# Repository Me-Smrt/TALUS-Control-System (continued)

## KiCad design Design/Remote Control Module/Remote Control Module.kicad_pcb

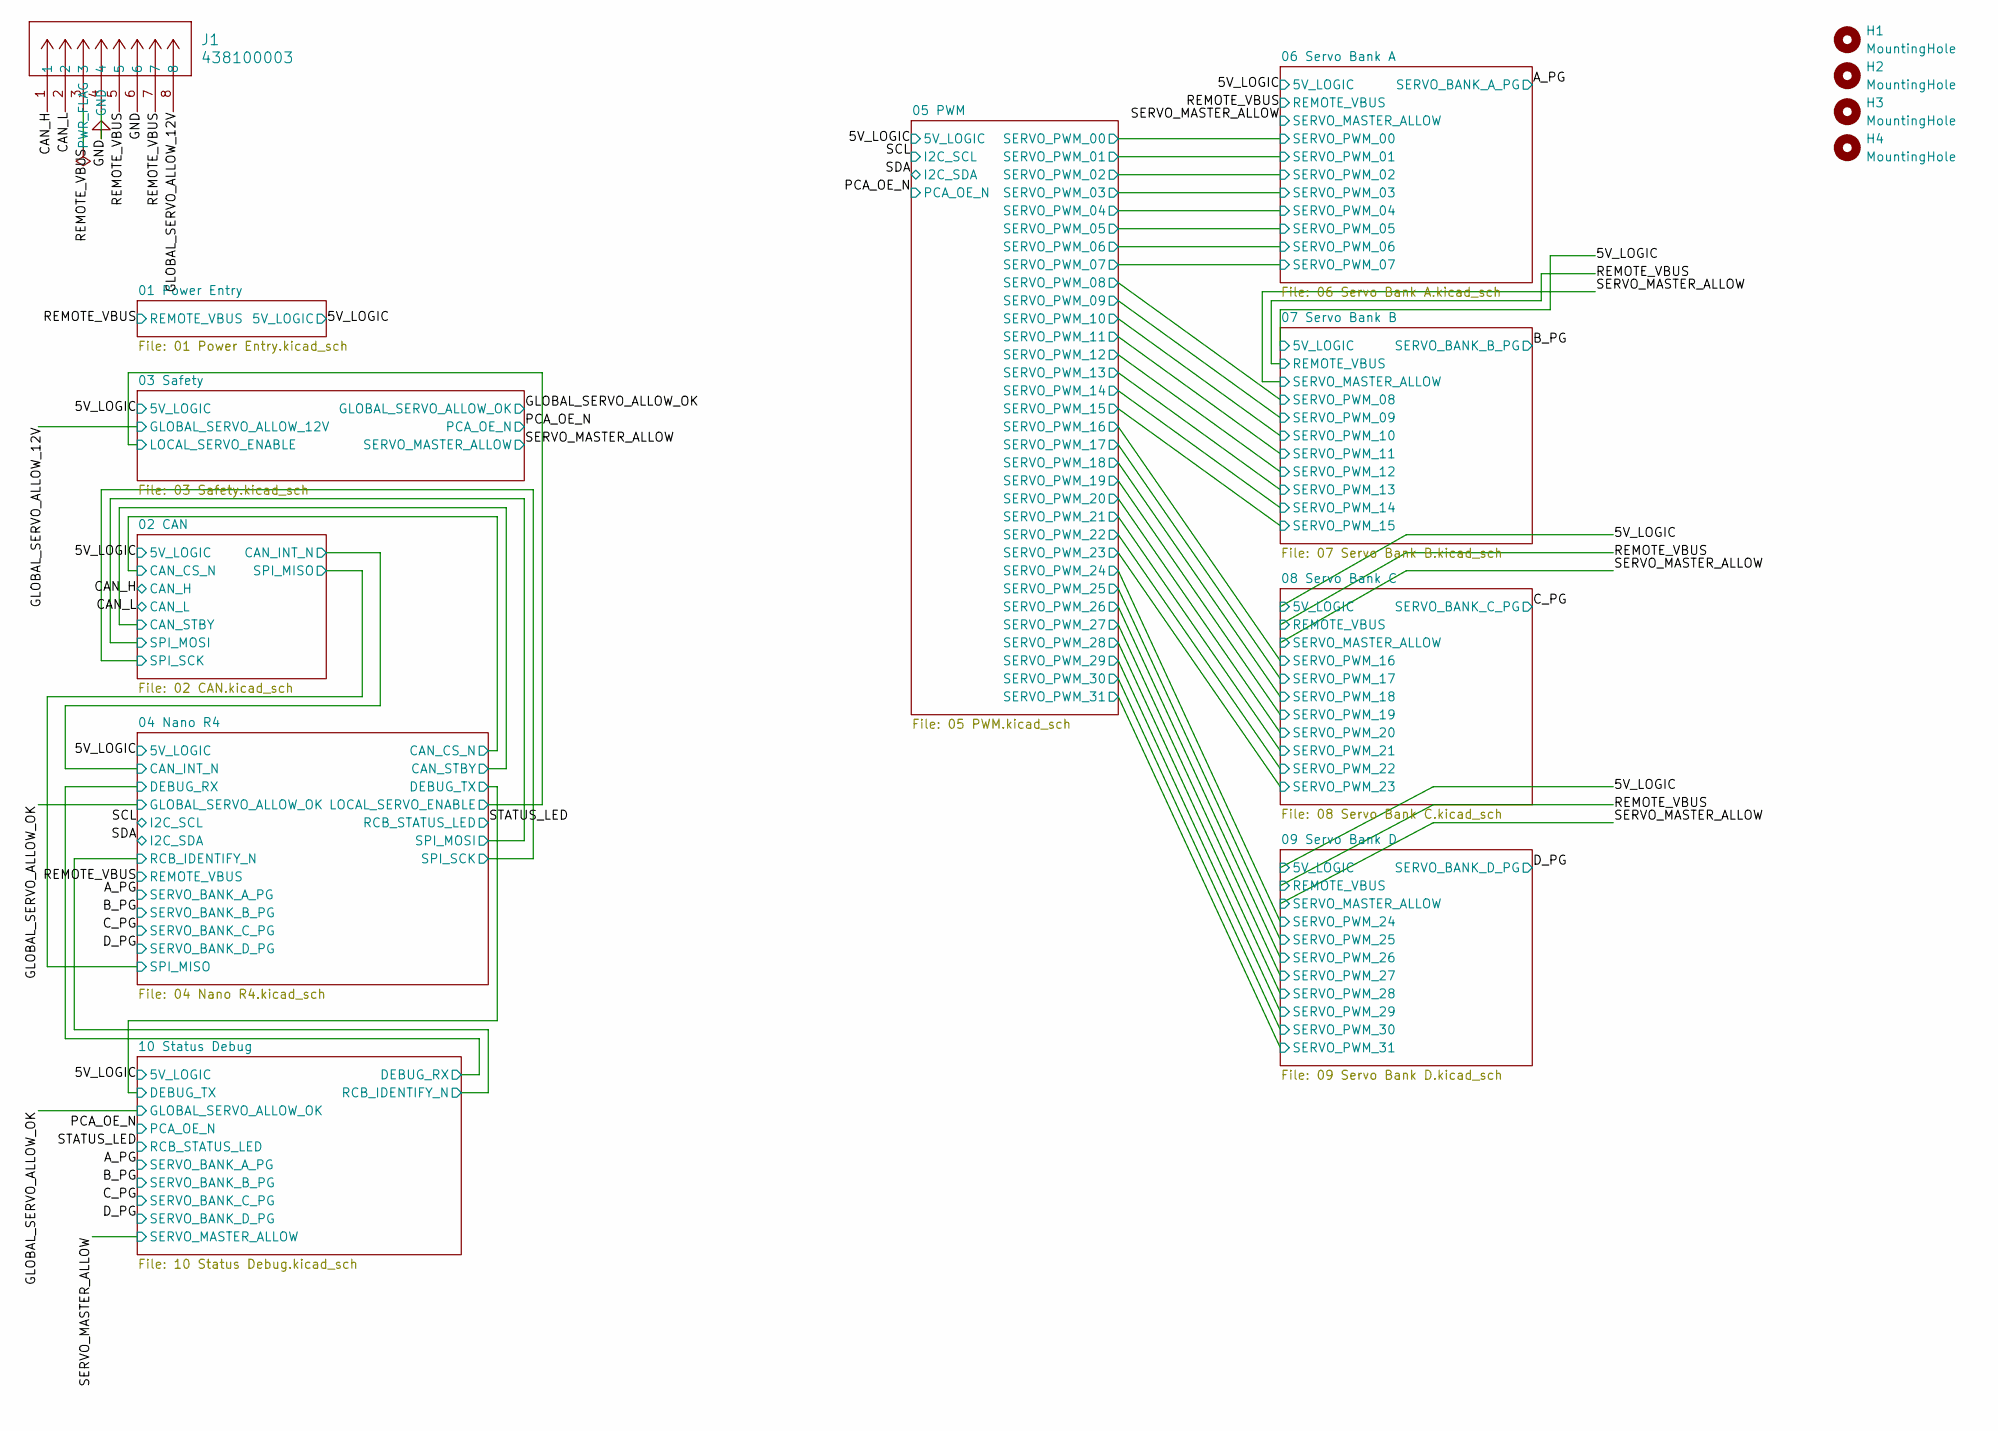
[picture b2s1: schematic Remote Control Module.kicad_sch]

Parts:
H1, H2, H3, H4: MountingHole; MountingHole_2.2mm_M2
J1: 438100003; CONN_SD-43810-011_08_CLIP_MOL; MPN 0438100003

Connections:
/CAN_H: J1.1; also elsewhere on the board
/CAN_L: J1.2; also elsewhere on the board
/GLOBAL_SERVO_ALLOW_12V: J1.8; also elsewhere on the board
/REMOTE_VBUS: J1.3, J1.5, J1.7; also elsewhere on the board
GND: J1.4, J1.6; also elsewhere on the board

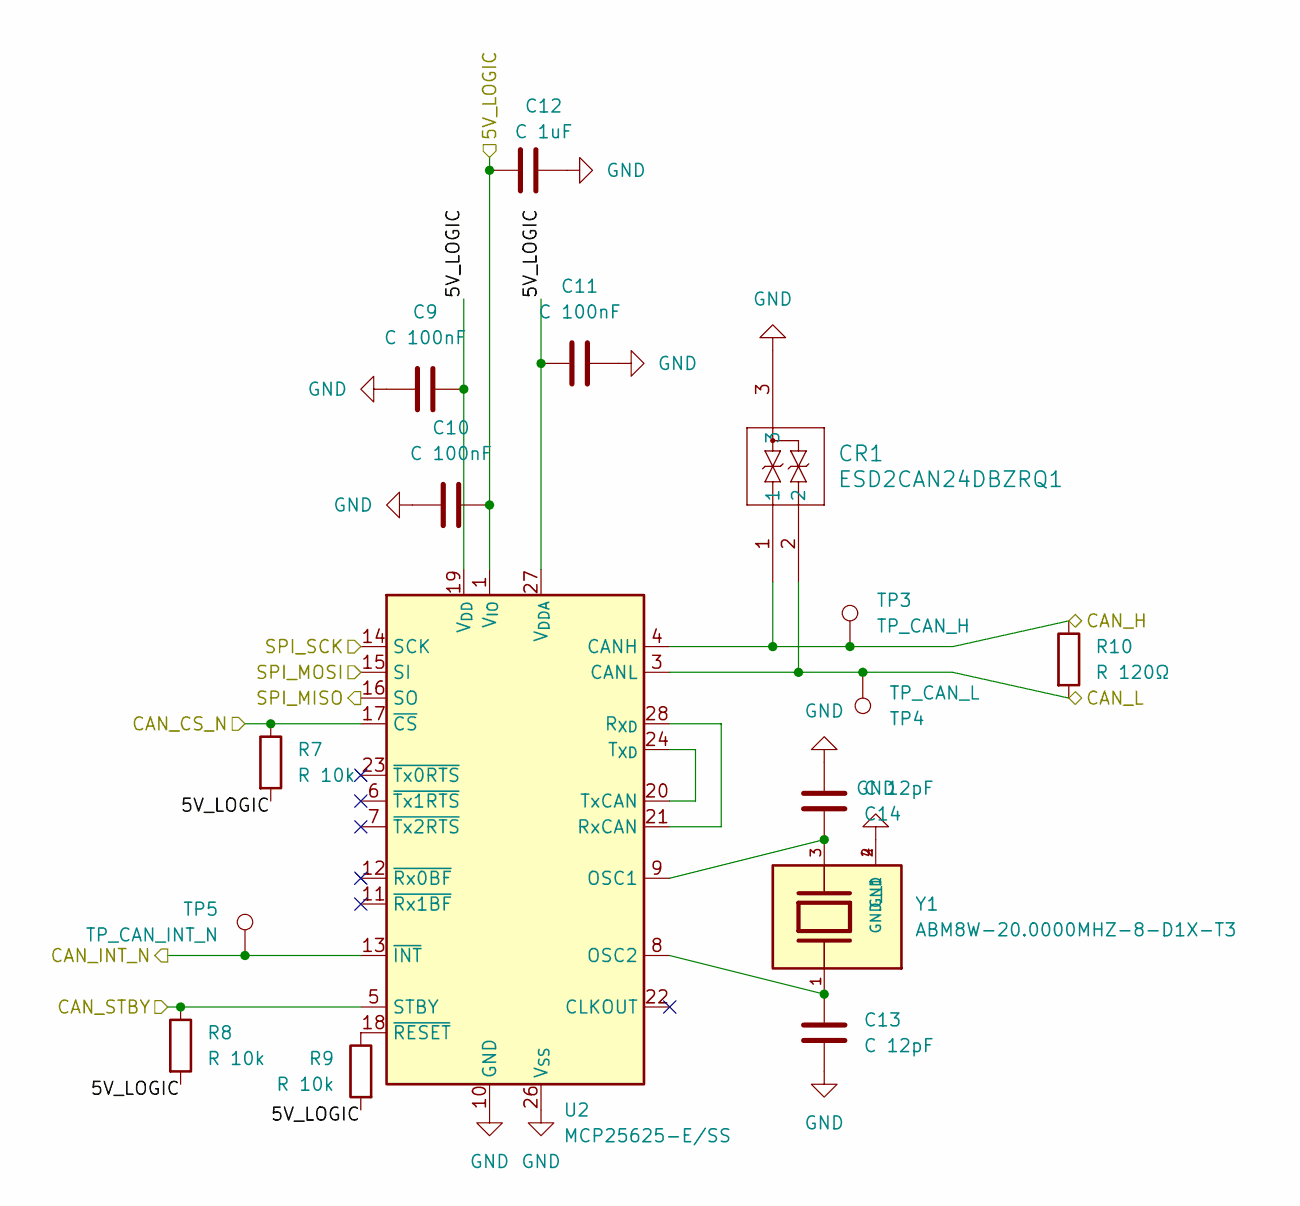
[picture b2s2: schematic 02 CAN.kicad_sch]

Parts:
C9, C10, C11: C 100nF; C_0603_1608Metric; MPN C0603C104K5RACAUTO
C12: C 1uF; C_0805_2012Metric; MPN CL21B105KBFNFNE
C13, C14: C 12pF; C_0603_1608Metric; MPN GRM1885C2A120JA01D
CR1: ESD2CAN24DBZRQ1; MPN ESD2CAN24DBZRQ1
R7, R8, R9: R 10k; R_0603_1608Metric; MPN RC0603FR-0710KL
R10: R 120Ω; R_0805_2012Metric; MPN RC0805FR-07120RL
TP3: TP_CAN_H; TestPoint_Pad_D1.5mm
TP4: TP_CAN_L; TestPoint_Pad_D1.5mm
TP5: TP_CAN_INT_N; TestPoint_Pad_D1.5mm
U2: MCP25625-E/SS; SSOP-28_5.3x10.2mm_P0.65mm; MPN MCP25625-E/SS
Y1: ABM8W-20.0000MHZ-8-D1X-T3; ABM8W 20 MHz; PARTREV 08.09.2018

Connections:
/02 CAN/CAN_CS_N: R7.1, U2.17 (~CS); also elsewhere on the board
/02 CAN/CAN_INT_N: TP5.1 (1_1), U2.13 (~INT); also elsewhere on the board
/02 CAN/CAN_STBY: R8.1, U2.5 (STBY); also elsewhere on the board
/02 CAN/SPI_MISO: U2.16 (SO); also elsewhere on the board
/02 CAN/SPI_MOSI: U2.15 (SI); also elsewhere on the board
/02 CAN/SPI_SCK: U2.14 (SCK); also elsewhere on the board
/5V_LOGIC: C9.2, C10.2, C11.2, C12.2, R7.2, R8.2, R9.2, U2.1 (V_{IO}), U2.19 (V_{DD}), U2.27 (V_{DDA}); also elsewhere on the board
/CAN_H: CR1.1, R10.1, TP3.1 (1_1), U2.4 (CANH); also elsewhere on the board
/CAN_L: CR1.2, R10.2, TP4.1 (1_1), U2.3 (CANL); also elsewhere on the board
GND: C9.1, C10.1, C11.1, C12.1, C13.2, C14.2, CR1.3, U2.10 (GND), U2.26 (V_{SS}), Y1.2 (GND), Y1.4 (GND__1); also elsewhere on the board
unnamed: C14.1, U2.9 (OSC1), Y1.3
unnamed: C13.1, U2.8 (OSC2), Y1.1
unnamed: U2.21 (RxCAN), U2.28 (R_{XD})
unnamed: U2.20 (TxCAN), U2.24 (T_{XD})
unnamed: R9.1, U2.18 (~RESET)

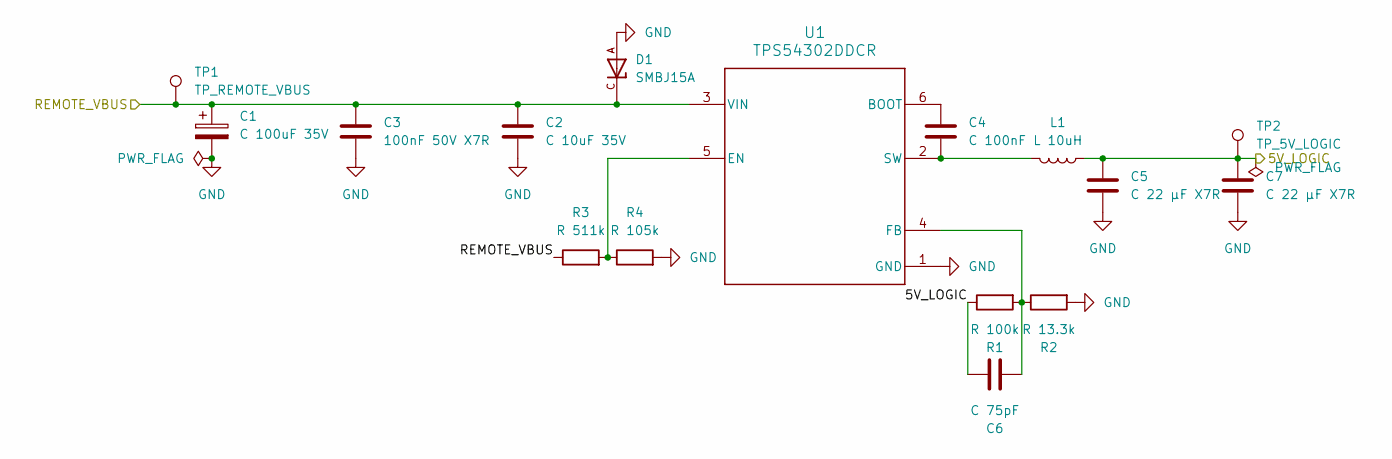
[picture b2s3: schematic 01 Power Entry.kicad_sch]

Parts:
C1: C 100uF 35V; EEEFK1V101P; MPN EEE-FK1V101P
C2: C 10uF 35V; C_1210_3225Metric; MPN CC1210KKX7RGBB106
C3: 100nF 50V X7R; C0603C104K5RACAUTO; MPN C0603C104K5RACAUTO
C4: C 100nF; C_0603_1608Metric; MPN C0603C104K5RACAUTO
C5, C7: C 22 µF X7R; C_1210_3225Metric; MPN GRM32ER71E226KE15L
C6: C 75pF; GRM1885C1H750JA01D; MPN GRM1885C2A750JA01D
D1: SMBJ15A; DIOM4336X265N; PARTREV F2102
L1: L 10uH; 7447714100; MPN 7447714100
R1: R 100k; R_0603_1608Metric; MPN RC0603FR-07100KL
R2: R 13.3k; R_0603_1608Metric; MPN RC0603FR-0713K3L
R3: R 511k; R_0603_1608Metric; MPN RC0603FR-07511KL
R4: R 105k; R_0603_1608Metric; MPN RC0603FR-07105KL
TP1: TP_REMOTE_VBUS; TestPoint_Pad_D1.5mm
TP2: TP_5V_LOGIC; TestPoint_Pad_D1.5mm
U1: TPS54302DDCR; MPN TPS54302DDCR

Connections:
/5V_LOGIC: C5.1, C6.1, C7.1, L1.1, R1.1, TP2.1 (1_1); also elsewhere on the board
/REMOTE_VBUS: C1.1, C2.1, C3.1, D1.C, R3.1, TP1.1 (1_1), U1.3 (VIN); also elsewhere on the board
GND: C1.2, C2.2, C3.2, C5.2, C7.2, D1.A, R2.2, R4.2, U1.1 (GND); also elsewhere on the board
unnamed: C4.1, U1.6 (BOOT)
unnamed: R3.2, R4.1, U1.5 (EN)
unnamed: C6.2, R1.2, R2.1, U1.4 (FB)
unnamed: C4.2, L1.2, U1.2 (SW)

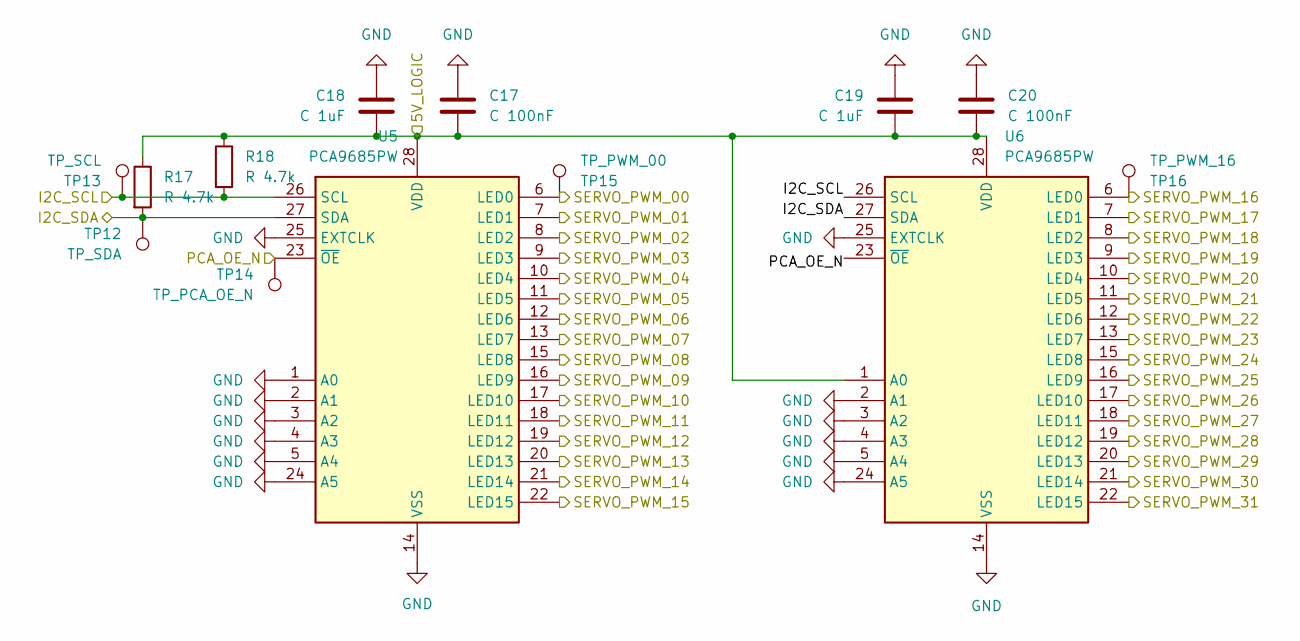
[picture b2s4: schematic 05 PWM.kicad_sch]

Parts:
C17, C20: C 100nF; C_0603_1608Metric; MPN C0603C104K5RACAUTO
C18, C19: C 1uF; C_0805_2012Metric; MPN CL21B105KBFNFNE
R17, R18: R 4.7k; R_0603_1608Metric; MPN RC0603FR-074K7L
TP12: TP_SDA; TestPoint_Pad_D1.5mm
TP13: TP_SCL; TestPoint_Pad_D1.5mm
TP14: TP_PCA_OE_N; TestPoint_Pad_D1.5mm
TP15: TP_PWM_00; TestPoint_Pad_D1.5mm
TP16: TP_PWM_16; TestPoint_Pad_D1.5mm
U5, U6: PCA9685PW; TSSOP-28_4.4x9.7mm_P0.65mm; MPN PCA9685PW,118

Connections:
/05 PWM/SERVO_PWM_00: TP15.1 (1_1), U5.6 (LED0); also elsewhere on the board
/05 PWM/SERVO_PWM_01: U5.7 (LED1); also elsewhere on the board
/05 PWM/SERVO_PWM_02: U5.8 (LED2); also elsewhere on the board
/05 PWM/SERVO_PWM_03: U5.9 (LED3); also elsewhere on the board
/05 PWM/SERVO_PWM_04: U5.10 (LED4); also elsewhere on the board
/05 PWM/SERVO_PWM_05: U5.11 (LED5); also elsewhere on the board
/05 PWM/SERVO_PWM_06: U5.12 (LED6); also elsewhere on the board
/05 PWM/SERVO_PWM_07: U5.13 (LED7); also elsewhere on the board
/05 PWM/SERVO_PWM_08: U5.15 (LED8); also elsewhere on the board
/05 PWM/SERVO_PWM_09: U5.16 (LED9); also elsewhere on the board
/05 PWM/SERVO_PWM_10: U5.17 (LED10); also elsewhere on the board
/05 PWM/SERVO_PWM_11: U5.18 (LED11); also elsewhere on the board
/05 PWM/SERVO_PWM_12: U5.19 (LED12); also elsewhere on the board
/05 PWM/SERVO_PWM_13: U5.20 (LED13); also elsewhere on the board
/05 PWM/SERVO_PWM_14: U5.21 (LED14); also elsewhere on the board
/05 PWM/SERVO_PWM_15: U5.22 (LED15); also elsewhere on the board
/05 PWM/SERVO_PWM_16: TP16.1 (1_1), U6.6 (LED0); also elsewhere on the board
/05 PWM/SERVO_PWM_17: U6.7 (LED1); also elsewhere on the board
/05 PWM/SERVO_PWM_18: U6.8 (LED2); also elsewhere on the board
/05 PWM/SERVO_PWM_19: U6.9 (LED3); also elsewhere on the board
/05 PWM/SERVO_PWM_20: U6.10 (LED4); also elsewhere on the board
/05 PWM/SERVO_PWM_21: U6.11 (LED5); also elsewhere on the board
/05 PWM/SERVO_PWM_22: U6.12 (LED6); also elsewhere on the board
/05 PWM/SERVO_PWM_23: U6.13 (LED7); also elsewhere on the board
/05 PWM/SERVO_PWM_24: U6.15 (LED8); also elsewhere on the board
/05 PWM/SERVO_PWM_25: U6.16 (LED9); also elsewhere on the board
/05 PWM/SERVO_PWM_26: U6.17 (LED10); also elsewhere on the board
/05 PWM/SERVO_PWM_27: U6.18 (LED11); also elsewhere on the board
/05 PWM/SERVO_PWM_28: U6.19 (LED12); also elsewhere on the board
/05 PWM/SERVO_PWM_29: U6.20 (LED13); also elsewhere on the board
/05 PWM/SERVO_PWM_30: U6.21 (LED14); also elsewhere on the board
/05 PWM/SERVO_PWM_31: U6.22 (LED15); also elsewhere on the board
/5V_LOGIC: C17.2, C18.2, C19.2, C20.2, R17.1, R18.1, U5.28 (VDD), U6.1 (A0), U6.28 (VDD); also elsewhere on the board
/PCA_OE_N: TP14.1 (1_1), U5.23 (~OE), U6.23 (~OE); also elsewhere on the board
/SCL: R18.2, TP13.1 (1_1), U5.26 (SCL), U6.26 (SCL); also elsewhere on the board
/SDA: R17.2, TP12.1 (1_1), U5.27 (SDA), U6.27 (SDA); also elsewhere on the board
GND: C17.1, C18.1, C19.1, C20.1, U5.1 (A0), U5.2 (A1), U5.3 (A2), U5.4 (A3), U5.5 (A4), U5.14 (VSS), U5.24 (A5), U5.25 (EXTCLK), U6.2 (A1), U6.3 (A2), U6.4 (A3), U6.5 (A4), U6.14 (VSS), U6.24 (A5), U6.25 (EXTCLK); also elsewhere on the board

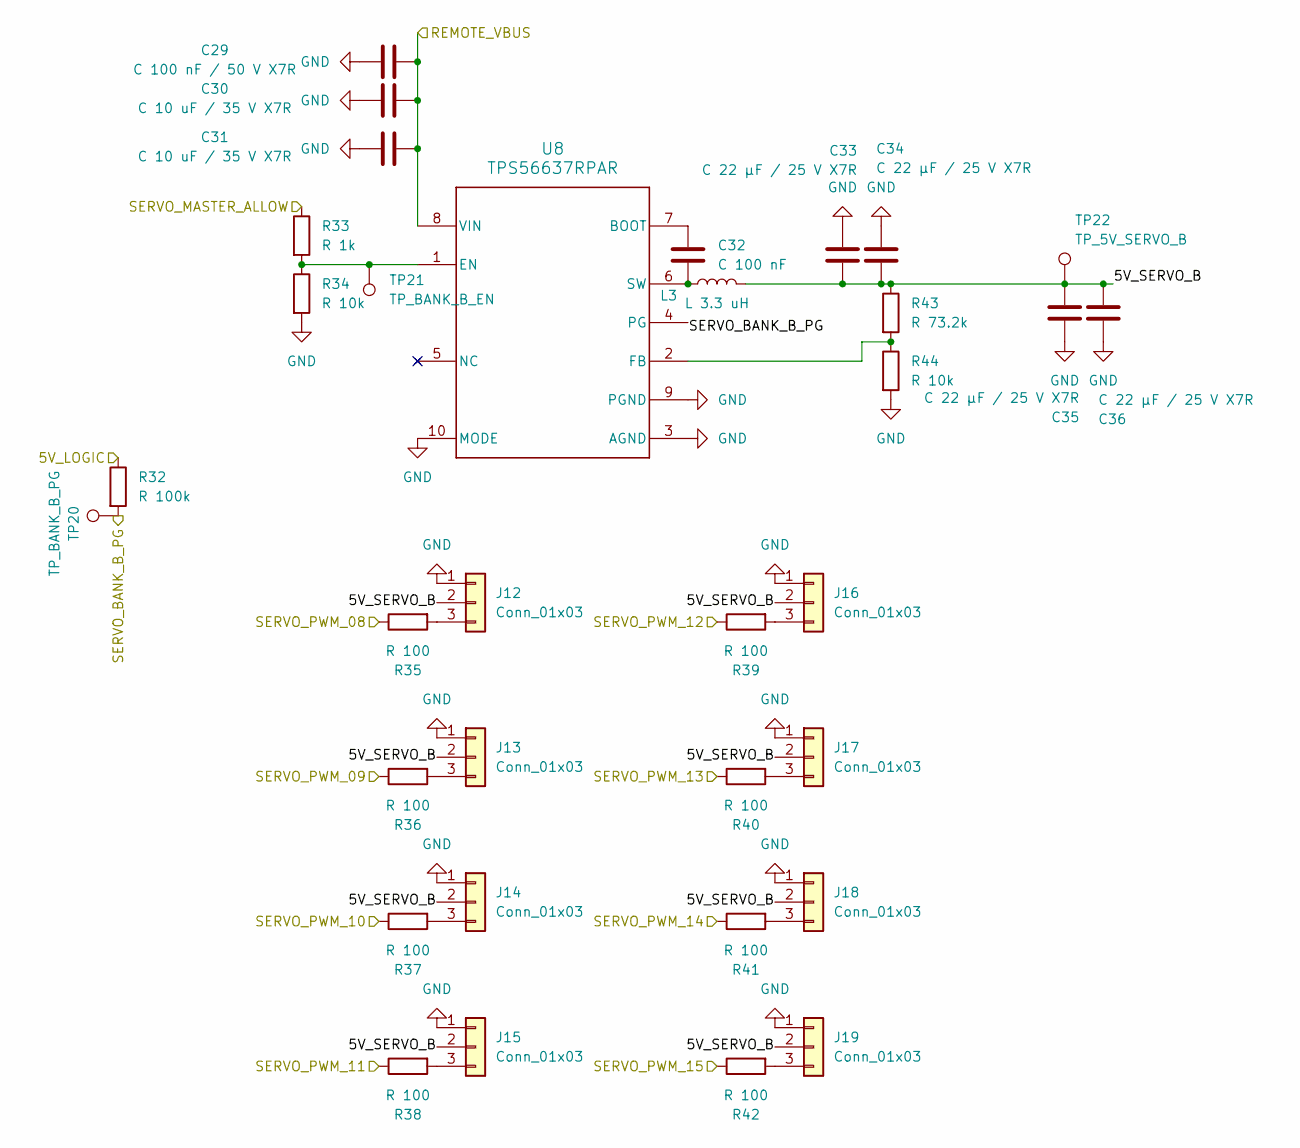
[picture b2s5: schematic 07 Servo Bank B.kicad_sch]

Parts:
C29: C 100 nF / 50 V X7R; C0603C104K5RACAUTO; MPN C0603C104K5RACAUTO
C30, C31: C 10 uF / 35 V X7R; C_1210_3225Metric; MPN CC1210KKX7RGBB106
C32: C 100 nF; C_0603_1608Metric; MPN C0603C104K5RACAUTO
C33, C34, C35, C36: C 22 µF / 25 V X7R; C_1210_3225Metric; MPN GRM32ER71E226KE15L
J12, J13, J14, J15, J16, J17, J18, J19: Conn_01x03; PinHeader_1x03_P2.54mm_Vertical_CompactSilk; MPN TSW-103-07-G-S
L3: L 3.3 uH; IND_IHLP-3232DZ_VIS; MPN IHLP3232DZER3R3M11
R32: R 100k; R_0603_1608Metric; MPN RC0603FR-07100KL
R33: R 1k; R_0603_1608Metric; MPN RC0603FR-071KL
R34, R44: R 10k; R_0603_1608Metric; MPN RC0603FR-0710KL
R35, R36, R37, R38, R39, R40, R41, R42: R 100; R_0603_1608Metric; MPN RC0603FR-07100RL
R43: R 73.2k; R_0603_1608Metric; MPN RC0603FR-0773K2L
TP20: TP_BANK_B_PG; TestPoint_Pad_D1.5mm
TP21: TP_BANK_B_EN; TestPoint_Pad_D1.5mm
TP22: TP_5V_SERVO_B; TestPoint_Pad_D1.5mm
U8: TPS56637RPAR; MPN TPS56637RPAR

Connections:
/05 PWM/SERVO_PWM_08: R35.1; also elsewhere on the board
/05 PWM/SERVO_PWM_09: R36.1; also elsewhere on the board
/05 PWM/SERVO_PWM_10: R37.1; also elsewhere on the board
/05 PWM/SERVO_PWM_11: R38.1; also elsewhere on the board
/05 PWM/SERVO_PWM_12: R39.1; also elsewhere on the board
/05 PWM/SERVO_PWM_13: R40.1; also elsewhere on the board
/05 PWM/SERVO_PWM_14: R41.1; also elsewhere on the board
/05 PWM/SERVO_PWM_15: R42.1; also elsewhere on the board
/5V_LOGIC: R32.1; also elsewhere on the board
/07 Servo Bank B/5V_SERVO_B: C33.2, C34.2, C35.2, C36.2, J12.2, J13.2, J14.2, J15.2, J16.2, J17.2, J18.2, J19.2, L3.2, R43.1, TP22.1 (1_1)
/B_PG: R32.2, TP20.1 (1_1), U8.4 (PG); also elsewhere on the board
/REMOTE_VBUS: C29.2, C30.2, C31.2, U8.8 (VIN); also elsewhere on the board
/SERVO_MASTER_ALLOW: R33.1; also elsewhere on the board
GND: C29.1, C30.1, C31.1, C33.1, C34.1, C35.1, C36.1, J12.1, J13.1, J14.1, J15.1, J16.1, J17.1, J18.1, J19.1, R34.2, R44.2, U8.3 (AGND), U8.9 (PGND), U8.10 (MODE); also elsewhere on the board
unnamed: J12.3, R35.2
unnamed: J13.3, R36.2
unnamed: J14.3, R37.2
unnamed: J15.3, R38.2
unnamed: J16.3, R39.2
unnamed: J17.3, R40.2
unnamed: J18.3, R41.2
unnamed: J19.3, R42.2
unnamed: C32.1, U8.7 (BOOT)
unnamed: R33.2, R34.1, TP21.1 (1_1), U8.1 (EN)
unnamed: R43.2, R44.1, U8.2 (FB)
unnamed: C32.2, L3.1, U8.6 (SW)

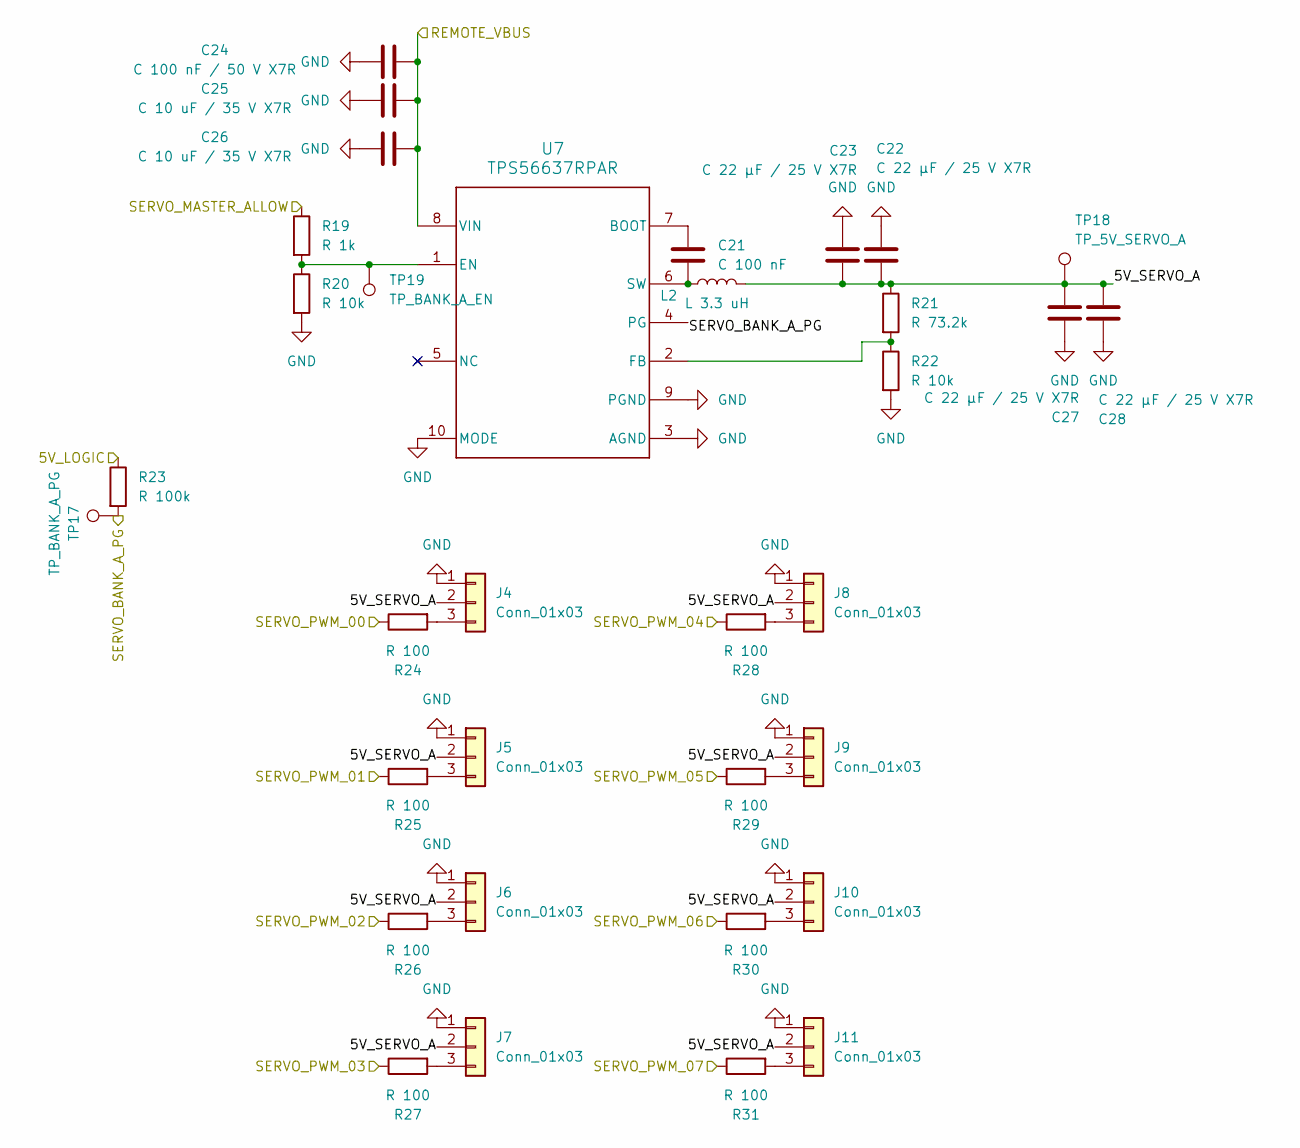
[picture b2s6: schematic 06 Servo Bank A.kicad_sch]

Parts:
C21: C 100 nF; C_0603_1608Metric; MPN C0603C104K5RACAUTO
C22, C23, C27, C28: C 22 µF / 25 V X7R; C_1210_3225Metric; MPN GRM32ER71E226KE15L
C24: C 100 nF / 50 V X7R; C0603C104K5RACAUTO; MPN C0603C104K5RACAUTO
C25, C26: C 10 uF / 35 V X7R; C_1210_3225Metric; MPN CC1210KKX7RGBB106
J4, J5, J6, J7, J8, J9, J10, J11: Conn_01x03; PinHeader_1x03_P2.54mm_Vertical_CompactSilk; MPN TSW-103-07-G-S
L2: L 3.3 uH; IND_IHLP-3232DZ_VIS; MPN IHLP3232DZER3R3M11
R19: R 1k; R_0603_1608Metric; MPN RC0603FR-071KL
R20, R22: R 10k; R_0603_1608Metric; MPN RC0603FR-0710KL
R21: R 73.2k; R_0603_1608Metric; MPN RC0603FR-0773K2L
R23: R 100k; R_0603_1608Metric; MPN RC0603FR-07100KL
R24, R25, R26, R27, R28, R29, R30, R31: R 100; R_0603_1608Metric; MPN RC0603FR-07100RL
TP17: TP_BANK_A_PG; TestPoint_Pad_D1.5mm
TP18: TP_5V_SERVO_A; TestPoint_Pad_D1.5mm
TP19: TP_BANK_A_EN; TestPoint_Pad_D1.5mm
U7: TPS56637RPAR; MPN TPS56637RPAR

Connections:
/05 PWM/SERVO_PWM_00: R24.1; also elsewhere on the board
/05 PWM/SERVO_PWM_01: R25.1; also elsewhere on the board
/05 PWM/SERVO_PWM_02: R26.1; also elsewhere on the board
/05 PWM/SERVO_PWM_03: R27.1; also elsewhere on the board
/05 PWM/SERVO_PWM_04: R28.1; also elsewhere on the board
/05 PWM/SERVO_PWM_05: R29.1; also elsewhere on the board
/05 PWM/SERVO_PWM_06: R30.1; also elsewhere on the board
/05 PWM/SERVO_PWM_07: R31.1; also elsewhere on the board
/5V_LOGIC: R23.1; also elsewhere on the board
/06 Servo Bank A/5V_SERVO_A: C22.2, C23.2, C27.2, C28.2, J4.2, J5.2, J6.2, J7.2, J8.2, J9.2, J10.2, J11.2, L2.2, R21.1, TP18.1 (1_1)
/A_PG: R23.2, TP17.1 (1_1), U7.4 (PG); also elsewhere on the board
/REMOTE_VBUS: C24.2, C25.2, C26.2, U7.8 (VIN); also elsewhere on the board
/SERVO_MASTER_ALLOW: R19.1; also elsewhere on the board
GND: C22.1, C23.1, C24.1, C25.1, C26.1, C27.1, C28.1, J4.1, J5.1, J6.1, J7.1, J8.1, J9.1, J10.1, J11.1, R20.2, R22.2, U7.3 (AGND), U7.9 (PGND), U7.10 (MODE); also elsewhere on the board
unnamed: J4.3, R24.2
unnamed: J5.3, R25.2
unnamed: J6.3, R26.2
unnamed: J7.3, R27.2
unnamed: J8.3, R28.2
unnamed: J9.3, R29.2
unnamed: J10.3, R30.2
unnamed: J11.3, R31.2
unnamed: C21.1, U7.7 (BOOT)
unnamed: R19.2, R20.1, TP19.1 (1_1), U7.1 (EN)
unnamed: R21.2, R22.1, U7.2 (FB)
unnamed: C21.2, L2.1, U7.6 (SW)

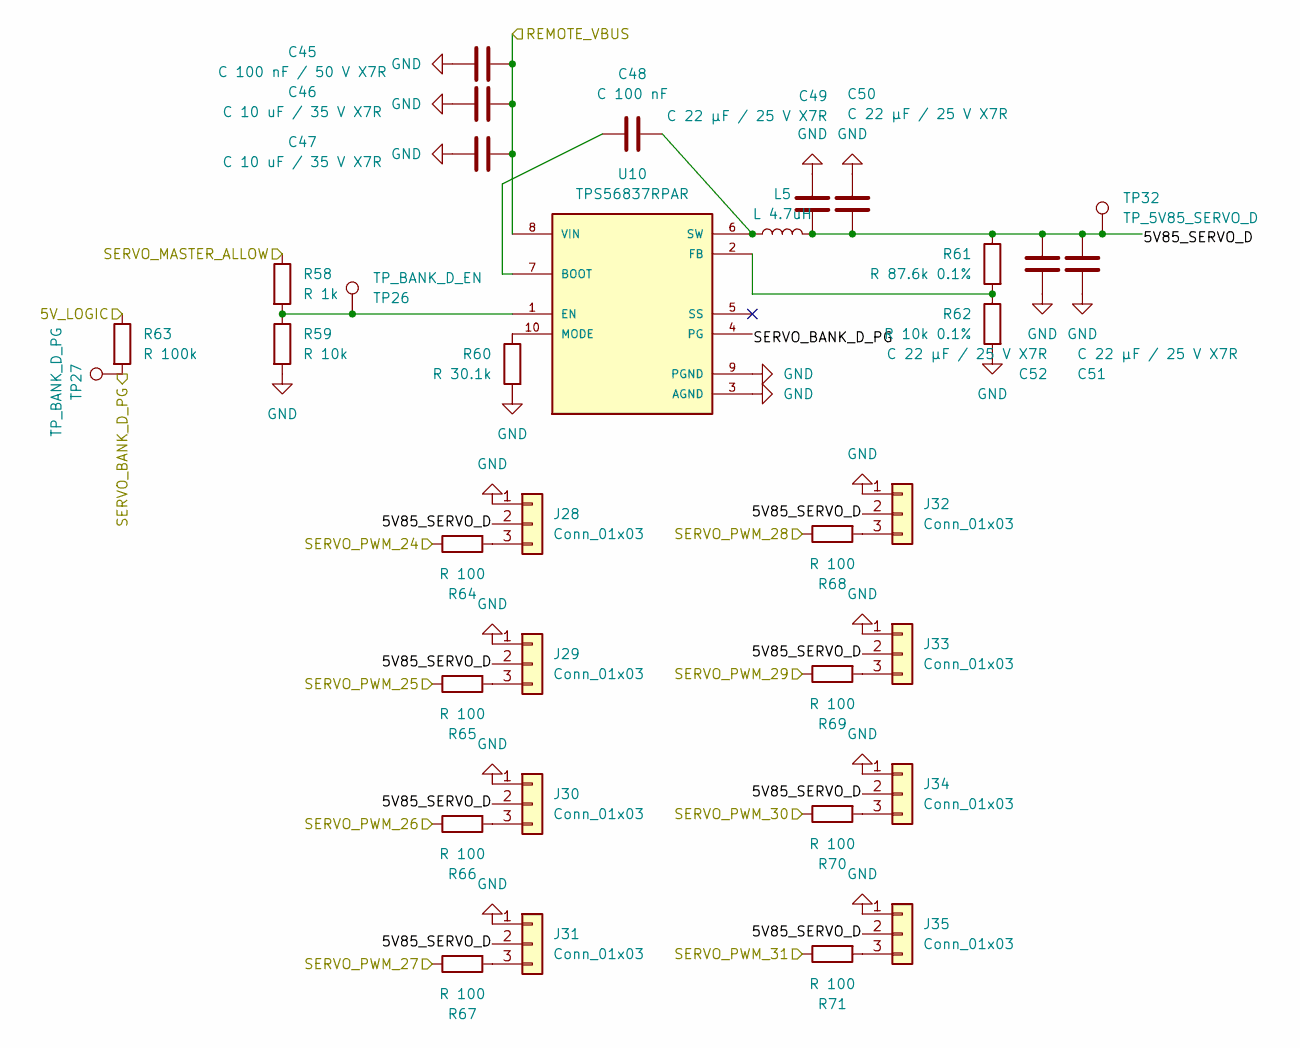
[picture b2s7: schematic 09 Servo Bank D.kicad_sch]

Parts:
C45: C 100 nF / 50 V X7R; C0603C104K5RACAUTO; MPN C0603C104K5RACAUTO
C46, C47: C 10 uF / 35 V X7R; C_1210_3225Metric; MPN CC1210KKX7RGBB106
C48: C 100 nF; C_0603_1608Metric; MPN C0603C104K5RACAUTO
C49, C50, C51, C52: C 22 µF / 25 V X7R; C_1210_3225Metric; MPN GRM32ER71E226KE15L
J28, J29, J30, J31, J32, J33, J34, J35: Conn_01x03; PinHeader_1x03_P2.54mm_Vertical_CompactSilk; MPN TSW-103-07-G-S
L5: L 4.7uH; WE-LHMI_1335; MPN 74437377047
R58: R 1k; R_0603_1608Metric; MPN RC0603FR-071KL
R59: R 10k; R_0603_1608Metric; MPN RC0603FR-0710KL
R60: R 30.1k; R_0603_1608Metric; MPN RC0603FR-0730K1L
R61: R 87.6k 0.1%; R_0603_1608Metric; MPN RT0603BRD0787K6L
R62: R 10k 0.1%; R_0603_1608Metric; MPN RT0603BRD0710KL
R63: R 100k; R_0603_1608Metric; MPN RC0603FR-07100KL
R64, R65, R66, R67, R68, R69, R70, R71: R 100; R_0603_1608Metric; MPN RC0603FR-07100RL
TP26: TP_BANK_D_EN; TestPoint_Pad_D1.5mm
TP27: TP_BANK_D_PG; TestPoint_Pad_D1.5mm
TP32: TP_5V85_SERVO_D; TestPoint_Pad_D1.5mm
U10: TPS56837RPAR; PARTREV A

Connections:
/05 PWM/SERVO_PWM_24: R64.1; also elsewhere on the board
/05 PWM/SERVO_PWM_25: R65.1; also elsewhere on the board
/05 PWM/SERVO_PWM_26: R66.1; also elsewhere on the board
/05 PWM/SERVO_PWM_27: R67.1; also elsewhere on the board
/05 PWM/SERVO_PWM_28: R68.1; also elsewhere on the board
/05 PWM/SERVO_PWM_29: R69.1; also elsewhere on the board
/05 PWM/SERVO_PWM_30: R70.1; also elsewhere on the board
/05 PWM/SERVO_PWM_31: R71.1; also elsewhere on the board
/5V_LOGIC: R63.1; also elsewhere on the board
/09 Servo Bank D/5V85_SERVO_D: C49.2, C50.2, C51.2, C52.2, J28.2, J29.2, J30.2, J31.2, J32.2, J33.2, J34.2, J35.2, L5.2, R61.1, TP32.1 (1_1)
/D_PG: R63.2, TP27.1 (1_1), U10.4 (PG); also elsewhere on the board
/REMOTE_VBUS: C45.2, C46.2, C47.2, U10.8 (VIN); also elsewhere on the board
/SERVO_MASTER_ALLOW: R58.1; also elsewhere on the board
GND: C45.1, C46.1, C47.1, C49.1, C50.1, C51.1, C52.1, J28.1, J29.1, J30.1, J31.1, J32.1, J33.1, J34.1, J35.1, R59.2, R60.2, R62.2, U10.3 (AGND), U10.9 (PGND); also elsewhere on the board
unnamed: J28.3, R64.2
unnamed: J29.3, R65.2
unnamed: J30.3, R66.2
unnamed: J31.3, R67.2
unnamed: J32.3, R68.2
unnamed: J33.3, R69.2
unnamed: J34.3, R70.2
unnamed: J35.3, R71.2
unnamed: C48.1, U10.7 (BOOT)
unnamed: R58.2, R59.1, TP26.1 (1_1), U10.1 (EN)
unnamed: R61.2, R62.1, U10.2 (FB)
unnamed: R60.1, U10.10 (MODE)
unnamed: C48.2, L5.1, U10.6 (SW)

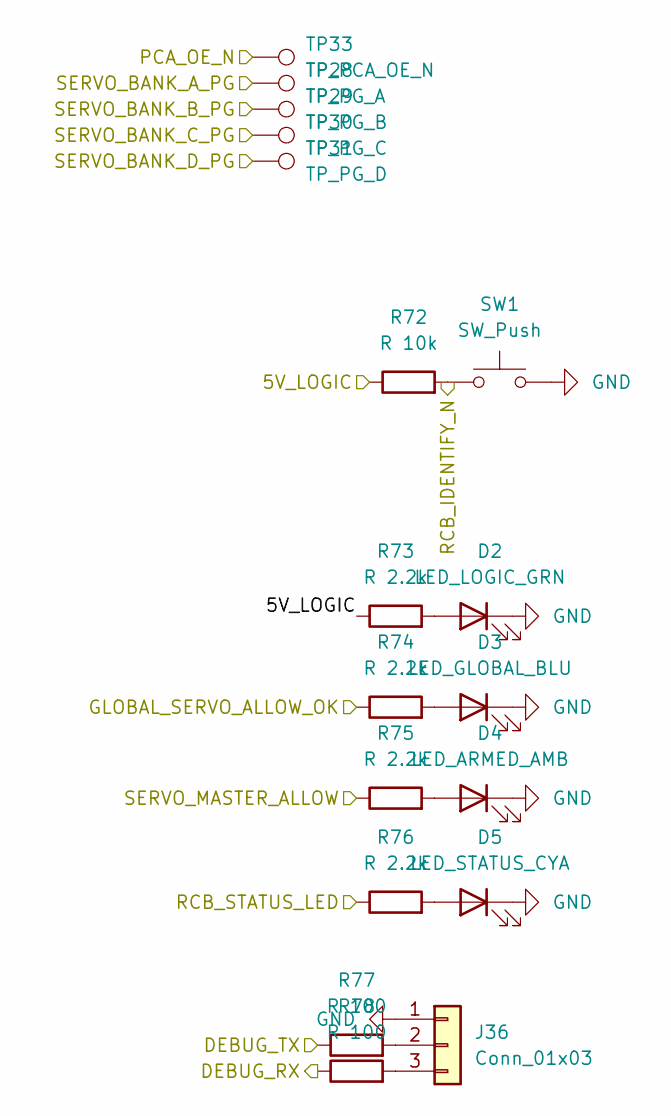
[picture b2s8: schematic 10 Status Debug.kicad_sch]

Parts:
D2: LED_LOGIC_GRN; LED_0805_2012Metric_CompactSilk; MPN LTST-C170KGKT
D3: LED_GLOBAL_BLU; LED_0805_2012Metric_CompactSilk; MPN LTST-C170TBKT
D4: LED_ARMED_AMB; LED_0805_2012Metric_CompactSilk; MPN LTST-C170KSKT
D5: LED_STATUS_CYA; LED_0805_2012Metric_CompactSilk; MPN 17-21UBGC/TR8
J36: Conn_01x03; PinHeader_1x03_P2.54mm_Vertical_CompactSilk; MPN TSW-103-07-G-S
R72: R 10k; R_0603_1608Metric; MPN RC0603FR-0710KL
R73, R74, R75, R76: R 2.2k; R_0603_1608Metric; MPN RC0603FR-072K2L
R77, R78: R 100; R_0603_1608Metric; MPN RC0603FR-07100RL
SW1: SW_Push; SW_PUSH_6mm; MPN B3F-1000
TP28: TP_PG_A; TestPoint_Pad_D1.5mm
TP29: TP_PG_B; TestPoint_Pad_D1.5mm
TP30: TP_PG_C; TestPoint_Pad_D1.5mm
TP31: TP_PG_D; TestPoint_Pad_D1.5mm
TP33: TP_PCA_OE_N; TestPoint_Pad_D1.5mm

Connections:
/04 Nano R4/DEBUG_RX: R78.1; also elsewhere on the board
/04 Nano R4/DEBUG_TX: R77.1; also elsewhere on the board
/04 Nano R4/RCB_IDENTIFY_N: R72.2, SW1.1; also elsewhere on the board
/5V_LOGIC: R72.1, R73.1; also elsewhere on the board
/A_PG: TP28.1 (1_1); also elsewhere on the board
/B_PG: TP29.1 (1_1); also elsewhere on the board
/C_PG: TP30.1 (1_1); also elsewhere on the board
/D_PG: TP31.1 (1_1); also elsewhere on the board
/GLOBAL_SERVO_ALLOW_OK: R74.1; also elsewhere on the board
/PCA_OE_N: TP33.1 (1_1); also elsewhere on the board
/SERVO_MASTER_ALLOW: R75.1; also elsewhere on the board
/STATUS_LED: R76.1; also elsewhere on the board
GND: D2.1 (K), D3.1 (K), D4.1 (K), D5.1 (K), J36.1, SW1.2; also elsewhere on the board
unnamed: D2.2 (A), R73.2
unnamed: D3.2 (A), R74.2
unnamed: D4.2 (A), R75.2
unnamed: D5.2 (A), R76.2
unnamed: J36.2, R77.2
unnamed: J36.3, R78.2

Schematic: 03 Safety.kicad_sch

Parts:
C15, C16: C 100nF; C_0603_1608Metric; MPN C0603C104K5RACAUTO
Q1: MMBT3904; SOT-23; MPN MMBT3904LT1G
R11: R 22k; R_0603_1608Metric; MPN RC0603FR-0722KL
R12, R14, R16: R 100k; R_0603_1608Metric; MPN RC0603FR-07100KL
R13, R15: R 10k; R_0603_1608Metric; MPN RC0603FR-0710KL
TP6: TP_GLOBAL_ALLOW_N; TestPoint_Pad_D1.5mm
TP7: TP_GLOBAL_SERVO_ALLOW_OK; TestPoint_Pad_D1.5mm
TP8: TP_LOCAL_SERVO_ENABLE; TestPoint_Pad_D1.5mm
TP9: TP_SERVO_MASTER_ALLOW; TestPoint_Pad_D1.5mm
TP10: TP_SERVO_POWER_ENABLE; TestPoint_Pad_D1.5mm
TP11: TP_PCA_OE_N; TestPoint_Pad_D1.5mm
U3: 74HC14; SOIC-14_3.9x8.7mm_P1.27mm; MPN 74HC14D,653
U4: 74AHC1G08; SOT-23-5; MPN 74AHC1G08GV,125

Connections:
/03 Safety/GLOBAL_ALLOW_N: Q1.3 (C), R13.2, TP6.1 (1_1), U3.1
/03 Safety/LOCAL_SERVO_ENABLE: R16.1, TP8.1 (1_1), U4.2; also elsewhere on the board
/5V_LOGIC: C15.1, C16.1, R13.1, R15.1, U3.14 (VCC), U4.5 (VCC); also elsewhere on the board
/GLOBAL_SERVO_ALLOW_12V: R11.1; also elsewhere on the board
/GLOBAL_SERVO_ALLOW_OK: TP7.1 (1_1), U3.2, U4.1; also elsewhere on the board
/PCA_OE_N: R15.2, TP11.1 (1_1), U3.4; also elsewhere on the board
/SERVO_MASTER_ALLOW: R14.1, TP9.1 (1_1), TP10.1 (1_1), U3.3, U4.4; also elsewhere on the board
GND: C15.2, C16.2, Q1.2 (E), R12.2, R14.2, R16.2, U3.5, U3.7 (GND), U3.9, U3.11, U3.13, U4.3 (GND); also elsewhere on the board
unnamed: Q1.1 (B), R11.2, R12.1

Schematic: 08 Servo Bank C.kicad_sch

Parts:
C37: C 100 nF / 50 V X7R; C0603C104K5RACAUTO; MPN C0603C104K5RACAUTO
C38, C39: C 10 uF / 35 V X7R; C_1210_3225Metric; MPN CC1210KKX7RGBB106
C40: C 100 nF; C_0603_1608Metric; MPN C0603C104K5RACAUTO
C41, C42, C43, C44: C 22 µF / 25 V X7R; C_1210_3225Metric; MPN GRM32ER71E226KE15L
J20, J21, J22, J23, J24, J25, J26, J27: Conn_01x03; PinHeader_1x03_P2.54mm_Vertical_CompactSilk; MPN TSW-103-07-G-S
L4: L 3.3 uH; IND_IHLP-3232DZ_VIS; MPN IHLP3232DZER3R3M11
R45: R 100k; R_0603_1608Metric; MPN RC0603FR-07100KL
R46: R 1k; R_0603_1608Metric; MPN RC0603FR-071KL
R47, R57: R 10k; R_0603_1608Metric; MPN RC0603FR-0710KL
R48, R49, R50, R51, R52, R53, R54, R55: R 100; R_0603_1608Metric; MPN RC0603FR-07100RL
R56: R 73.2k; R_0603_1608Metric; MPN RC0603FR-0773K2L
TP23: TP_BANK_C_PG; TestPoint_Pad_D1.5mm
TP24: TP_BANK_C_EN; TestPoint_Pad_D1.5mm
TP25: TP_5V_SERVO_C; TestPoint_Pad_D1.5mm
U9: TPS56637RPAR; MPN TPS56637RPAR

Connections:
/05 PWM/SERVO_PWM_16: R48.1; also elsewhere on the board
/05 PWM/SERVO_PWM_17: R49.1; also elsewhere on the board
/05 PWM/SERVO_PWM_18: R50.1; also elsewhere on the board
/05 PWM/SERVO_PWM_19: R51.1; also elsewhere on the board
/05 PWM/SERVO_PWM_20: R52.1; also elsewhere on the board
/05 PWM/SERVO_PWM_21: R53.1; also elsewhere on the board
/05 PWM/SERVO_PWM_22: R54.1; also elsewhere on the board
/05 PWM/SERVO_PWM_23: R55.1; also elsewhere on the board
/5V_LOGIC: R45.1; also elsewhere on the board
/08 Servo Bank C/5V_SERVO_C: C41.2, C42.2, C43.2, C44.2, J20.2, J21.2, J22.2, J23.2, J24.2, J25.2, J26.2, J27.2, L4.2, R56.1, TP25.1 (1_1)
/C_PG: R45.2, TP23.1 (1_1), U9.4 (PG); also elsewhere on the board
/REMOTE_VBUS: C37.2, C38.2, C39.2, U9.8 (VIN); also elsewhere on the board
/SERVO_MASTER_ALLOW: R46.1; also elsewhere on the board
GND: C37.1, C38.1, C39.1, C41.1, C42.1, C43.1, C44.1, J20.1, J21.1, J22.1, J23.1, J24.1, J25.1, J26.1, J27.1, R47.2, R57.2, U9.3 (AGND), U9.9 (PGND), U9.10 (MODE); also elsewhere on the board
unnamed: J20.3, R48.2
unnamed: J21.3, R49.2
unnamed: J22.3, R50.2
unnamed: J23.3, R51.2
unnamed: J24.3, R52.2
unnamed: J25.3, R53.2
unnamed: J26.3, R54.2
unnamed: J27.3, R55.2
unnamed: C40.1, U9.7 (BOOT)
unnamed: R46.2, R47.1, TP24.1 (1_1), U9.1 (EN)
unnamed: R56.2, R57.1, U9.2 (FB)
unnamed: C40.2, L4.1, U9.6 (SW)
